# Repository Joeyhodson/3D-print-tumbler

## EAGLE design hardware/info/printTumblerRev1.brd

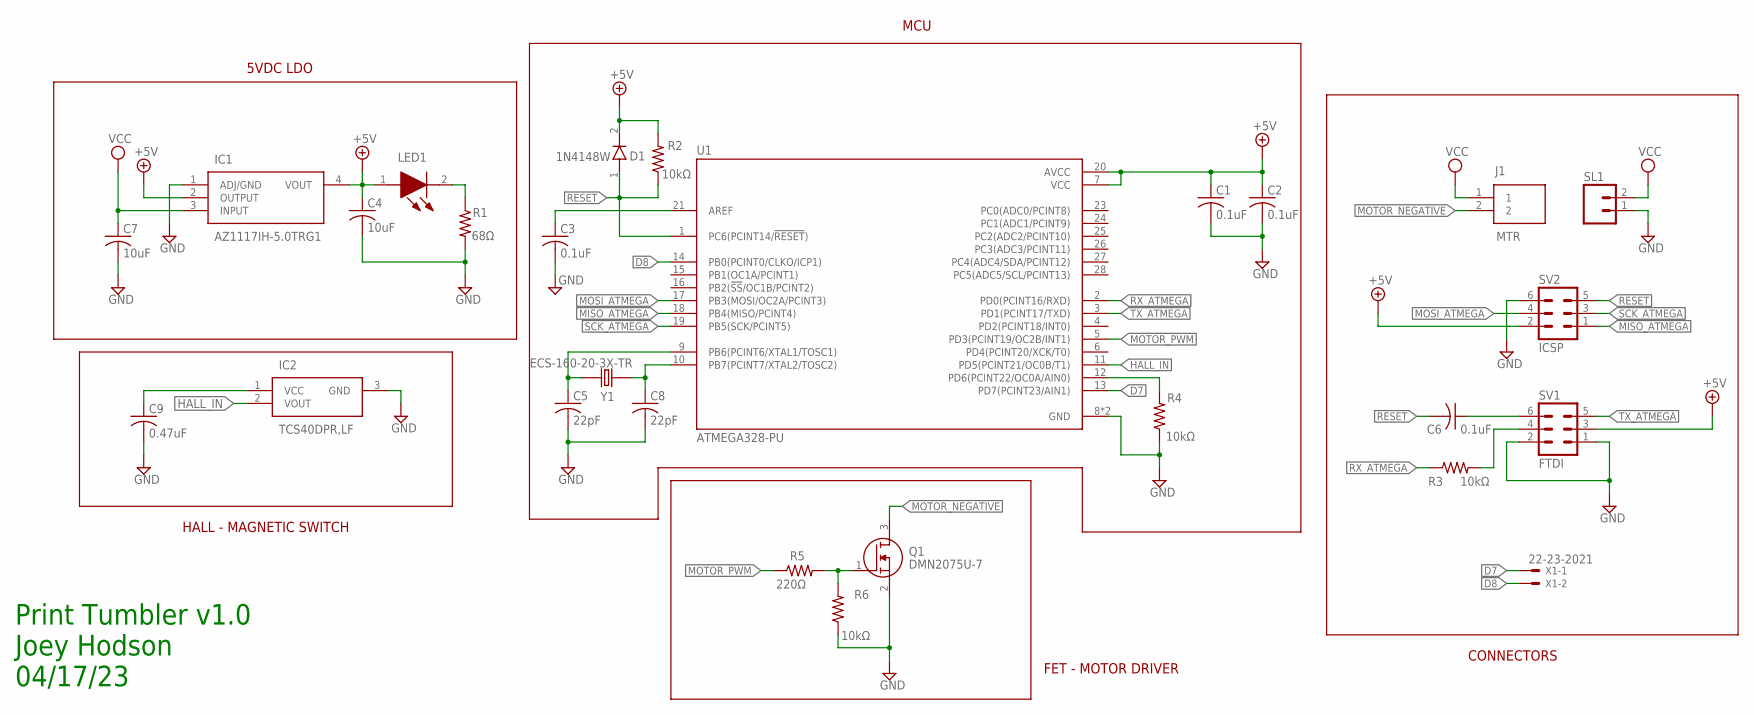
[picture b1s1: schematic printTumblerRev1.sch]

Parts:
C1, C2, C3, C6: 0.1uF; C0603
C4, C7: 10uF; C0805
C5, C8: 22pF; C0603
C9: 0.47uF; C0603
D1: 1N4148W; SOD523F
IC1: AZ1117IH-5.0TRG1; SOT230P700X170-4N
IC2: TCS40DPR,LF; SOTFL95P240X88-3N
J1: MTR; SHDR2W90P0X381_1X2_802X740X850
LED1: SML-LX0603IW-TR; SMLLX0603IWTR
Q1: DMN2075U-7; SOT96P240X100-3N
R1: 68Ω; R0603
R2, R3, R4, R6: 10kΩ; R0603
R5: 220Ω; R0603
SL1: M02; 02P
SV1: FTDI; MA03-2
SV2: ICSP; MA03-2
U1: ATMEGA328-PU; DIP787W46P254L3467H508Q28
X1: 22-23-2021
Y1: ECS-160-20-3X-TR; XTAL_ECS-160-20-3X-TR

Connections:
+5V: C1.1, C2.1, C4.1, D1.2 (C1), IC1.2 (OUTPUT), IC1.4 (VOUT), LED1.1 (A), R2.2, SV1.3, SV2.2, U1.7 (VCC), U1.20 (AVCC)
D7: U1.13 (PD7(PCINT23/AIN1)), X1.1
D8: U1.14 (PB0(PCINT0/CLKO/ICP1)), X1.2
GND: C1.2, C2.2, C3.2, C4.2, C5.2, C7.2, C8.2, C9.2, IC1.1 (ADJ/GND), IC2.3 (GND), Q1.2 (S), R1.2, R4.1, R6.1, SL1.1, SV1.1, SV1.2, SV2.6, U1.8 (GND), U1.22 (GND)
HALL_IN: IC2.2 (VOUT), U1.11 (PD5(PCINT21/OC0B/T1))
MISO_ATMEGA: SV2.1, U1.18 (PB4(MISO/PCINT4))
MOSI_ATMEGA: SV2.4, U1.17 (PB3(MOSI/OC2A/PCINT3))
MOTOR_NEGATIVE: J1.2, Q1.3 (D)
MOTOR_PWM: R5.1, U1.5 (PD3(PCINT19/OC2B/INT1))
unnamed: C3.1, U1.21 (AREF)
unnamed: LED1.2 (K), R1.1
unnamed: C6.1, SV1.6
unnamed: R3.2, SV1.4
unnamed: C5.1, U1.9 (PB6(PCINT6/XTAL1/TOSC1)), Y1.2
unnamed: C8.1, U1.10 (PB7(PCINT7/XTAL2/TOSC2)), Y1.1
unnamed: C9.1, IC2.1 (VCC)
unnamed: R4.2, U1.12 (PD6(PCINT22/OC0A/AIN0))
unnamed: Q1.1 (G), R5.2, R6.2
RESET: C6.2, D1.1 (A1), R2.1, SV2.5, U1.1 (PC6(PCINT14/!RESET!))
RX_ATMEGA: R3.1, U1.2 (PD0(PCINT16/RXD))
SCK_ATMEGA: SV2.3, U1.19 (PB5(SCK/PCINT5))
TX_ATMEGA: SV1.5, U1.3 (PD1(PCINT17/TXD))
VCC: C7.1, IC1.3 (INPUT), J1.1, SL1.2

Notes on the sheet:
Print Tumbler v1.0 Joey Hodson 04/17/23
5VDC LDO
MCU
FET - MOTOR DRIVER
CONNECTORS
HALL - MAGNETIC SWITCH

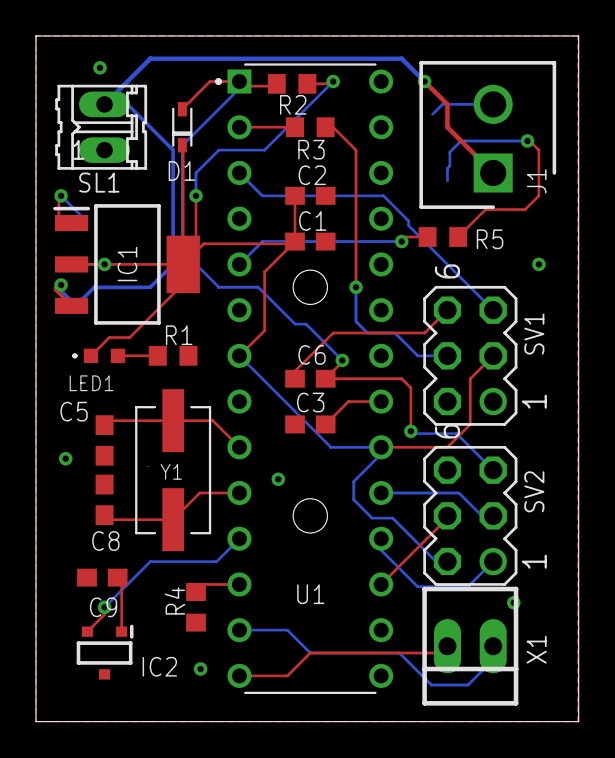
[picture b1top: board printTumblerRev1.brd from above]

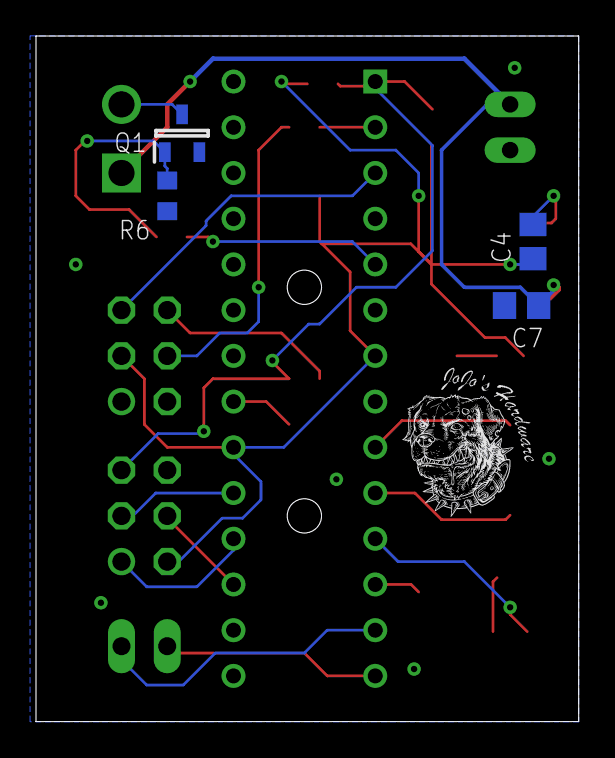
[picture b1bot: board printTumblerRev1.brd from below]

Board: 2 copper layers, 30.1 x 38.1 mm, 27 parts (4 on the bottom side), 23 nets.

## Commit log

2023-04-17 Adding directory structure
2023-04-18 Added 1st revision gerber
